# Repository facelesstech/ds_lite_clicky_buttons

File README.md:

# ds_lite_clicky_buttons
ds_lite_clicky_buttons

Blog post - https://facelesstech.wordpress.com/2022/07/23/ds-lite-clicky-buttons/

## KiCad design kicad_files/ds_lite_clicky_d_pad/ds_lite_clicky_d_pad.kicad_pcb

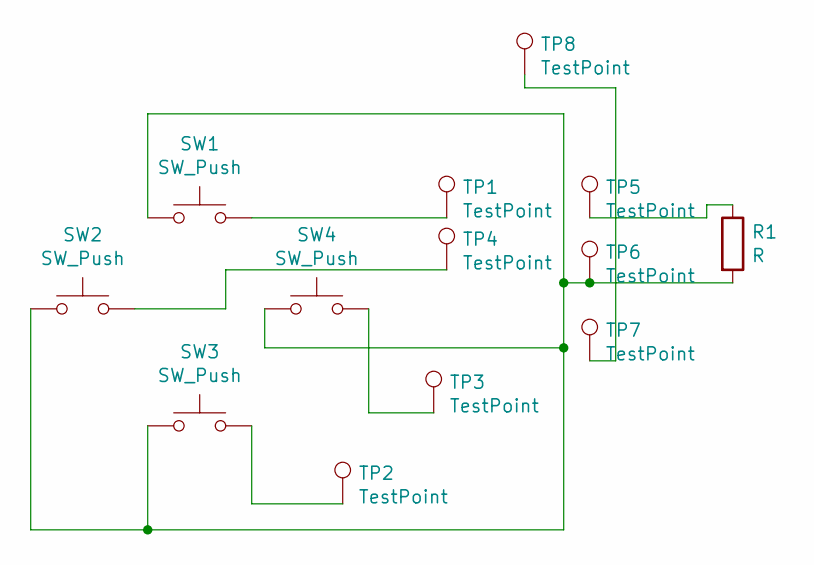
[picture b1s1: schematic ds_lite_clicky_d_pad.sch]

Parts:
R1: R; R_0603_1608Metric_Pad0.98x0.95mm_HandSolder
SW1, SW2, SW3, SW4: SW_Push; gba_sp_buttons
TP1, TP2, TP3, TP4, TP5, TP6, TP7: TestPoint; 1mm_test_point
TP8: TestPoint; 2mm_test_point_smd

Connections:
unnamed: R1.1, TP5.1
unnamed: R1.2, SW1.1, SW2.1, SW3.1, SW4.1, TP6.1
unnamed: SW1.2, TP1.1
unnamed: SW2.2, TP4.1
unnamed: SW3.2, TP2.1
unnamed: SW4.2, TP3.1
unnamed 6: TP7.1, TP8.1; also elsewhere on the board

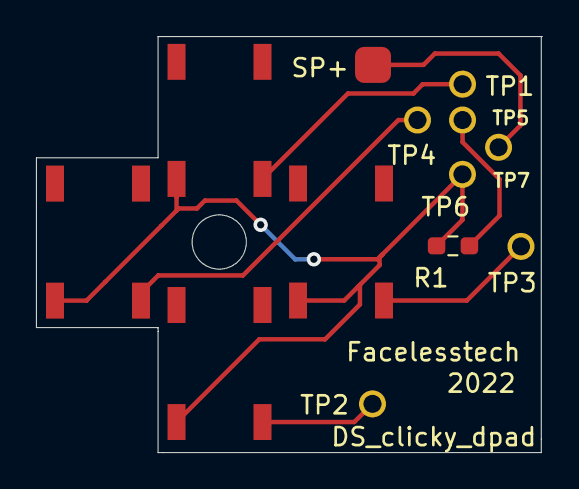
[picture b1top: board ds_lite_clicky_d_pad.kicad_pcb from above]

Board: 2 copper layers, 28.1 x 23.1 mm, 13 parts (0 on the bottom side), 7 nets.

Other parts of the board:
SP+: TestPoint; 2mm_test_point_smd

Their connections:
unnamed 6: SP+.1; also elsewhere on the board

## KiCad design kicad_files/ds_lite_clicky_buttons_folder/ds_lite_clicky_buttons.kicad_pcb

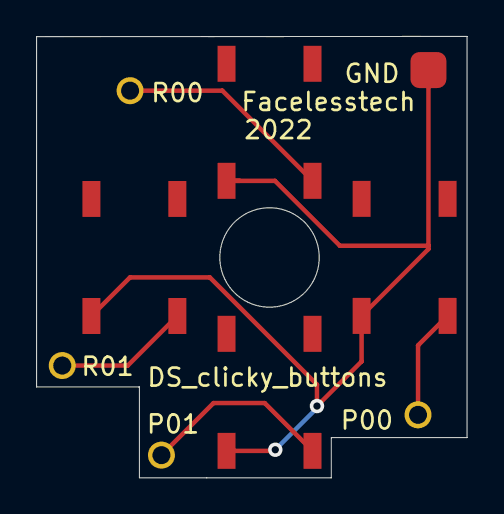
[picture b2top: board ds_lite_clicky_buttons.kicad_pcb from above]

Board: 2 copper layers, 23.9 x 24.5 mm, 9 parts (0 on the bottom side), 5 nets.

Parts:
GND: TestPoint; 2mm_test_point_smd
P00, P01: TestPoint; 1mm_test_point
R00, R01: TestPoint; 1mm_test_point
SW1, SW2, SW3, SW4: SW_Push; gba_sp_buttons

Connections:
unnamed: GND.1, SW1.1, SW2.1, SW3.1, SW4.1
unnamed: R00.1, SW1.2
unnamed: R01.1, SW2.2
unnamed: P01.1, SW3.2
unnamed: P00.1, SW4.2

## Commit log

2022-07-23 setting the license
2022-07-23 added PCB files
2022-08-20 moved files
2022-08-20 added d-pad files
2022-10-16 added photo
2022-10-16 added photo to readme
2022-10-16 added photo to readme1
2022-10-16 added photo to readme2
